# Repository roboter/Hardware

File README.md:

# HardwareModules
List of all my arduinos, ESPs, STM32s modules

## Directories

### [Arduino](/Arduino)
Various Arduino boards and development kits including Nano, Pro Mini, Leonardo, ATTINY85, and custom development boards.
<br/>

### [AVR](/AVR)
AVR microcontroller development boards and tools including Butterfly and STK500 programmer.
<br/>

### [CH582F](/CH582F)
CH582F microcontroller development resources.
<br/>

### [COMPONENTS](/COMPONENTS)
Hardware components including displays (SSD1306), sensors (WS2812, WS2812B, YF923), and linear sensors.
<br/>

### [Cypress](/Cypress)
Cypress microcontroller development boards including CY8CKIT-059.
<br/>

### [Displays](/Displays)
Display modules and libraries including:
* 1.7" SPI 128x160 OLED ST7735
* TM1637 Digital Tube LED Clock Display
* UTFT for Arduino Mega (PlatformIO)
* HD44780 LCD displays
* Nokia LCD5110 (PCD8544)
* SSD1306 OLED displays
* ST7789 TFT displays
* GM12864 GLCD modules
<br/>

### [EINK](/EINK)
E-ink display modules including Lilygo T5-4.7 inch displays.
<br/>

### [ESP](/ESP)
ESP32 and ESP8266 development boards including:
* Heltec WiFi Kit 8
* ESP32TTGO-OLED-18650
* TS V1.0 Esp32 1.44 TFT Display
* Wemos with Display
* ESP-01, ESP-03, ESP32-CAM
* T-Display-S3
* Various TTGO boards
<br/>

### [Geehy](/Geehy)
Geehy APM32 microcontroller development boards and SDKs.
<br/>

### [GigaDevice](/GigaDevice)
GigaDevice GD32 microcontroller boards including GD32VF103 (RISC-V) and GD32E232K.
<br/>

### [IC](/IC)
Integrated circuit datasheets and documentation.
<br/>

### [Modules](/Modules)
Various electronic modules including:
* Battery management modules
* CC1101 RF modules
* CP2102 USB-to-UART converters
* DS3231 RTC modules
* NRF24L01 wireless modules
* VS1053B MP3 player modules
* Motor drivers (A3967, l9110)
* Display modules (MAX7219, 8x8 RGB boards)
* And many more...
<br/>

### [NORDIC](/NORDIC)
Nordic Semiconductor development boards including nRF52810, nRF52833, and Embeetle boards.
<br/>

### [NXP](/NXP)
NXP microcontroller development boards including FRDM-K22F and FRDM-KL27Z.
<br/>

### [PROJECTS](/PROJECTS)
Complete hardware projects including LoRaWAN LR1262 designs with KiCad schematics and PCB files.
<br/>

### [Raspberry](/Raspberry)
Raspberry Pi RP2040-based boards including RP2040-Matrix and RP2040-Tiny.
<br/>

### [SHIELDS](/SHIELDS)
Arduino shields including:
* Multi Function Shield
* OPEN-SMART Rich Shield TWO
* VS153 MP3 Shield
* ZYA0031 IoT Training Kit
* Joystick shields
<br/>

### [STM32](/STM32)
STM32 microcontroller development boards including:
* BluePill, BlackPill
* NUCLEO series (F303K8, C031C6, L152RE, H563ZI)
* Discovery boards (F3DISCOVERY, F429-Discovery, F746G-Discovery)
* Mini development boards
* STM32F407VET6, STM32F103C8T6 variants
* WeAct Black Pill V3.0
* STLink programmer/debugger
<br/>

### [STM8](/STM8)
STM8 microcontroller development boards and documentation including STM8S103F3 development board.
<br/>

### [WCH](/WCH)
WCH microcontroller boards including CH32V003 series (RISC-V) development kits and examples.
<br/>

---

## Featured Boards

### Displays
* [1,7 SPI 128x160 OLED ST7735 <br/>
](/Displays/1,7_SPI_128x160_OLED_ST7735)

* <a href="/Displays/TM1637"> 4 Bits TM1637 Digital Tube LED Clock Display Module For Arduino Due UNO 2560 R3 <br/> </a>

* <a href="/Displays/UTFT"> UTFT for arduino mega (Paltformio) <br/>
</a>

### ESP
* <a href="ESP/HELTEC"> Heltec WiFi Kit 8 <br/> 
</a>
* <a href="ESP/ESP32TTGO-OLED-18650">ESP32TTGO-OLED-18650 <br/>
</a>

* <a href="ESP/TTGO">TS V1.0 Esp32 1.44 TFT Display MicroSD Card Slot Speakers WIFI Bluetooth Module <br/></a>

* <a href="ESP/Wemos-32-With-OLED">Wemos with Display<br/></a>

### STM32
* <a href="/STM32">STM32</a>

### STLink
* <a href="/STM32/STLink">STLink v2<br/></a>

### STM8 
* <a href="/STM8">STM8s103F3 Development board<br/>
 </a>

### Arduino
* <a href="/Arduino/Digistump-ATTINY85">Digistump ATTINY85<br/></a>

### GD32
* <a href="GigaDevice/GD32VF103">GD32VF103<br/></a>

### Cypress
* <a href="/Cypress/CY8CKIT-059">CY8CKIT-059<br/></a>

### Shields (arduino)
* <a href="SHIELDS/Multi_Function_Shield">Multi function Shield<br/></a>

### Battery Charger
* Battery charger modules can be found in [Modules/battery modules](/Modules/battery%20modules/)

### Modules
* <a href="/Modules/CP2102">CP2102 Micro USB to UART TTL Module 6Pin Serial Converter STC Replace FT232<br/></a>

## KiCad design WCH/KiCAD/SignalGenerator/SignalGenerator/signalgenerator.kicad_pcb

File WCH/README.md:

# WCH

This directory contains WCH (Nanjing Qinheng Microelectronics) microcontroller development boards and resources.

See [wiring.md](wiring.md) for general WCH (RISC-V) wiring and programming notes.

## Contents

### CH32V003-DEV-KIT
CH32V003 development kit based on RISC-V architecture. Contains:
<br/>
- Development board schematics
- Datasheets and reference manuals
- Example projects with SSD1306 OLED display
- I2C communication examples

### CH32V003EVT
CH32V003 evaluation board examples including:
- GPIO, UART, SPI, I2C examples
- Timer and PWM examples
- ADC and DMA examples
- Flash programming examples
- System configuration examples

### CH32V003J4M6
CH32V003J4M6 variant examples including:
- Blink examples
- Neopixel WS2812 examples
- KiCad project files
<br/>

### ch32v003f4p6-SignalGenerator
Complete signal generator project using CH32V003 and SI5351 clock generator chip. Includes:
- SI5351 driver implementation
- SSD1306 OLED display driver
- Documentation and schematics

### KiCAD
KiCad PCB design projects:
- CH32V003J4M6 development board
- Signal generator board design
- NE555 timer projects
- Gerber files for manufacturing

### Documentation
- CH32V003 datasheets and reference manuals
- WCH-Link programmer schematics
- Board pinout diagrams

All CH32V003 boards are based on RISC-V architecture, providing an open-source alternative to ARM Cortex-M0 microcontrollers.

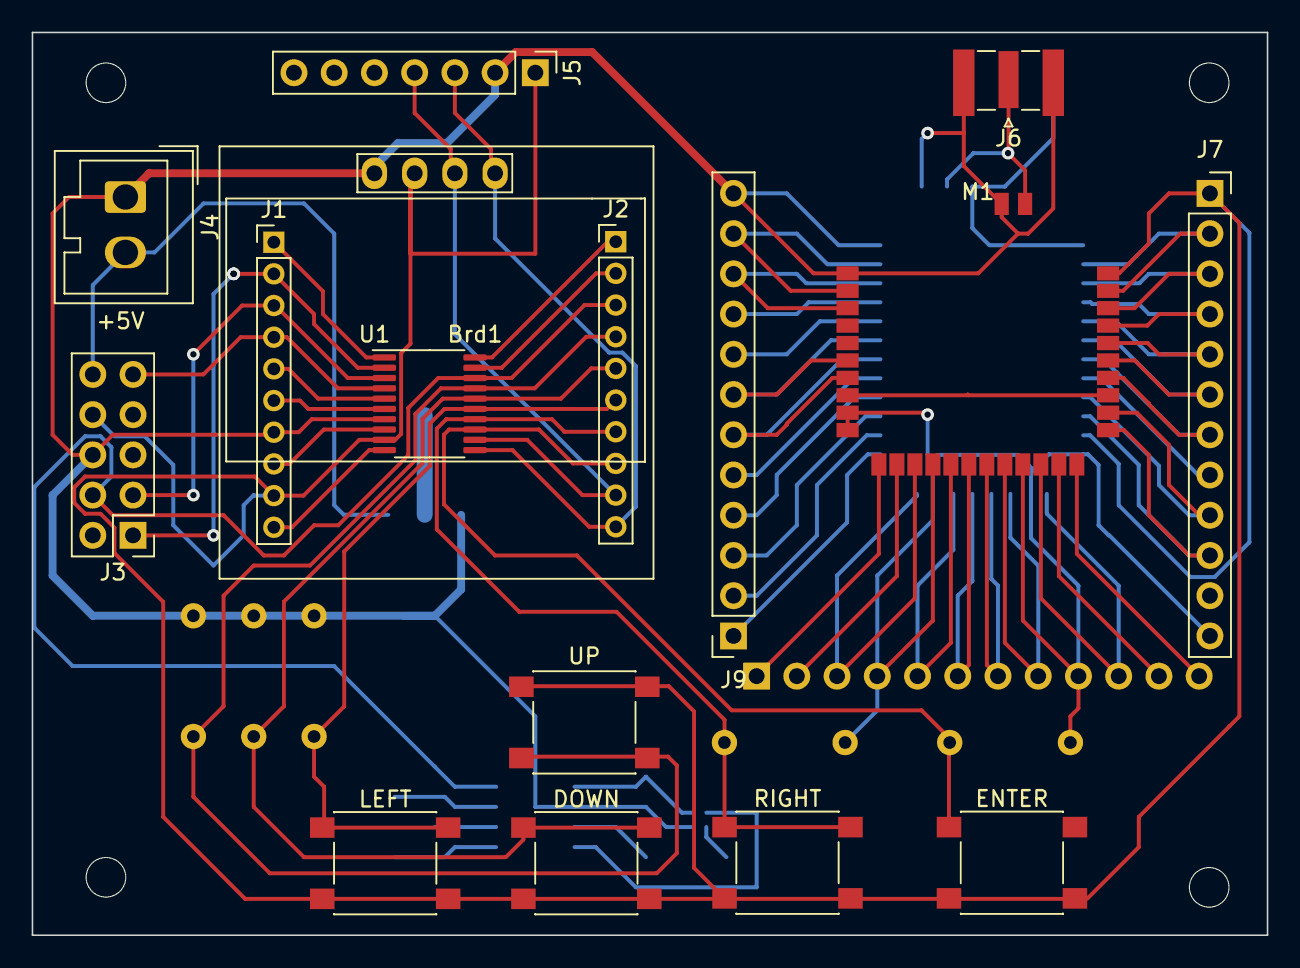
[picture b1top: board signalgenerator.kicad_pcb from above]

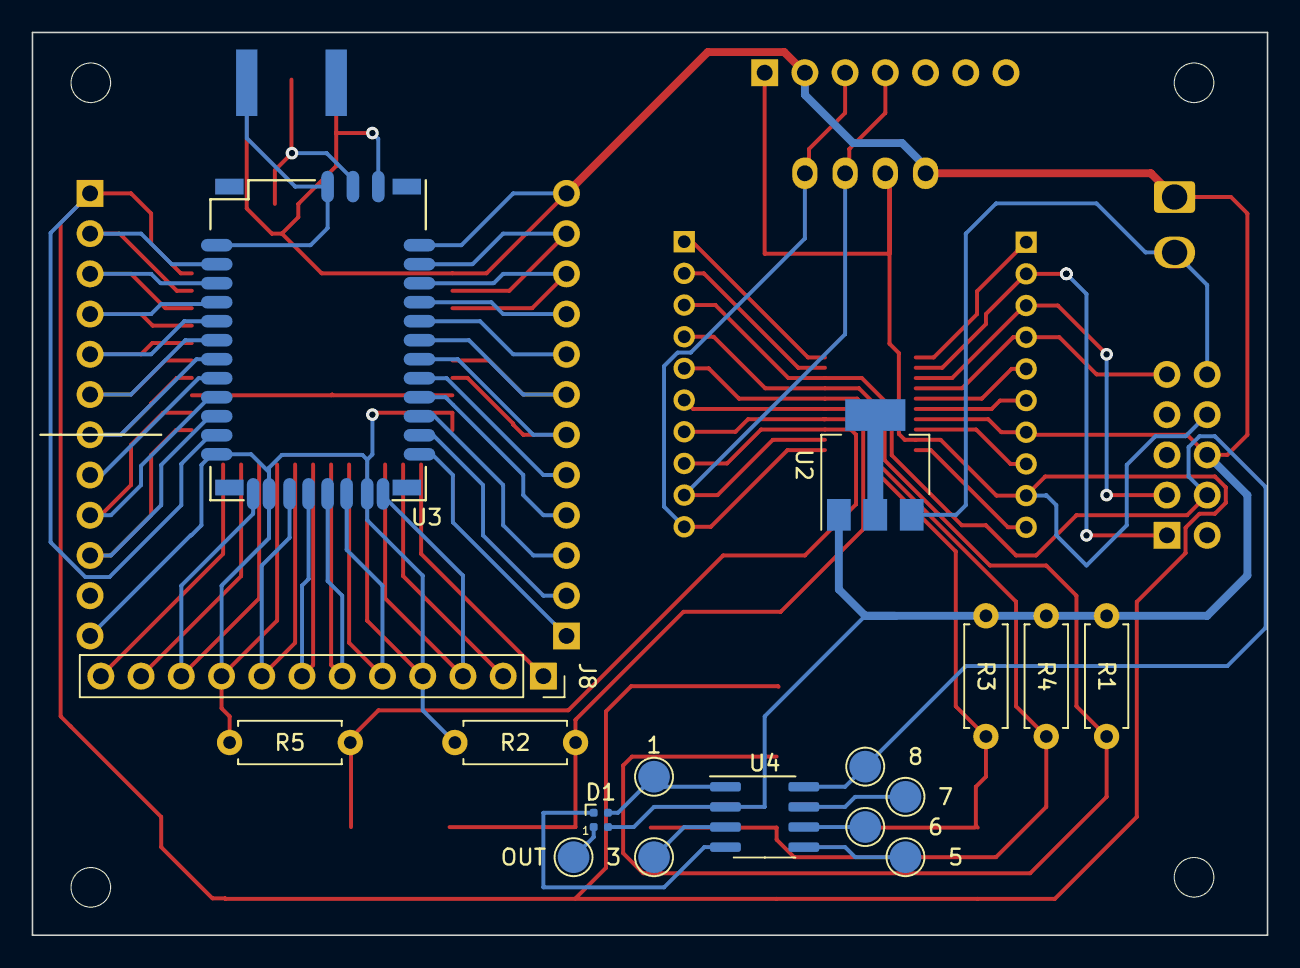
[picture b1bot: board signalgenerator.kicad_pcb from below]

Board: 2 copper layers, 78.0 x 57.0 mm, 33 parts (17 on the bottom side), 60 nets.

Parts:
1, 3, 5, 6, 7, 8: PC1; TestPoint_Pad_D2.0mm
Brd1: SSD1306; 128x64OLED
D1: SK6805; LED_SK6812_EC15_1.5x1.5mm
DOWN: RIGHT; SW_Push_1P1T_NO_6x6mm_H9.5mm
ENTER: ENTER; SW_Push_1P1T_NO_6x6mm_H9.5mm
J1, J2: Conn_01x10; PinHeader_1x10_P2.00mm_Vertical
J3: Conn_02x05_Odd_Even; PinHeader_2x05_P2.54mm_Vertical
J4: Conn_01x02; Wago_734-132_1x02_P3.50mm_Vertical
J5: Conn_01x07_Pin; PinHeader_1x07_P2.54mm_Vertical
J6: Conn_Coaxial; SMA_Samtec_SMA-J-P-X-ST-EM1_EdgeMount
J7, J8, J9: Conn_01x12; PinSocket_1x12_P2.54mm_Vertical
LEFT: LEFT; SW_Push_1P1T_NO_6x6mm_H9.5mm
M1: LR1262
OUT: PC1; TestPoint_Pad_D2.0mm
R1, R2, R3, R4, R5: 1K; R_Axial_DIN0207_L6.3mm_D2.5mm_P7.62mm_Horizontal
RIGHT: DOWN; SW_Push_1P1T_NO_6x6mm_H9.5mm
U1: CH32V003F4P6; TSSOP-20_4.4x6.5mm_P0.65mm
U2: AMS1117-3.3; SOT-223-3_TabPin2
U3: RN42N
U4: CH32V003J4M6; SOIC-8_3.9x4.9mm_P1.27mm
UP: UP; SW_Push_1P1T_NO_6x6mm_H9.5mm

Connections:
+3.3V: Brd1.2 (VCC), D1.4 (VDD), DOWN.2, ENTER.2, J1.9, J3.8, J5.1, J7.1, LEFT.2, M1.32 (3v3), RIGHT.2, U1.9 (VDD), U2.2 (VO), U3.11 (VDD), U4.4 (VDD), UP.2
+5V: J3.10, J4.2, U2.3 (VI)
/DOWN: J2.7, R2.1, RIGHT.1, U1.14 (PC4)
/ENTER: ENTER.1, J2.8, R5.1, U1.13 (PC3)
/LEFT: J2.6, LEFT.1, R3.1, U1.15 (PC5)
/RIGHT: DOWN.1, J2.5, R4.1, U1.16 (PC6)
/RST: J1.4, J3.9, U1.4 (PD7)
/RX: J1.2, J3.1, U1.2 (PD5)
/SCL: Brd1.3 (SCL), J2.9, J5.4, U1.12 (PC2)
/SDA: Brd1.4 (SDA), J2.10, J5.3, U1.11 (PC1)
/SWDIO: 8.1, J2.3, J3.4, U1.18 (PD1), U4.8 (PD1/PD4/PD5)
/TX: J1.3, J3.3, U1.3 (PD6)
/UP: J2.4, R1.1, U1.17 (PC7), UP.1
GND: Brd1.1 (GND), D1.2 (VSS), J1.7, J3.6, J4.1, J5.2, J6.2 (Ext), J7.12, J9.12, M1.1 (GND), M1.4 (GND), M1.5 (GND), M1.9 (GND), M1.10 (GND), M1.34 (GND), R1.2, R2.2, R3.2, R4.2, R5.2, U1.7 (VSS), U2.1 (GND), U3.1 (GND), U3.12 (GND), U3.25 (GND), U3.27 (GND), U3.28 (GND), U3.29 (GND), U4.2 (VSS)
J7_3: J7.10, M1.23 (UART-TX), U3.10 (PCM_OUT)
J7_4: J7.9, M1.24 (UART-RX), U3.9 (PCM_IN)
J7_5: J7.8, U3.8 (PCM_SYNC)
J7_6: J7.7, M1.26 (LPUART-RX), U3.7 (PCM_CLK)
J7_7: J7.6, M1.27 (PA8), U3.6 (SPI_CLK)
J7_8: J7.5, M1.28 (MOSI), U3.5 (RESET)
J7_9: J7.4, M1.29 (MISO), U3.4 (GPIO7)
J7_10: J7.3, M1.30 (SCK), U3.3 (GPIO6)
J7_11: J7.2, M1.31 (CS), U3.2 (SPI_MOSI)
J8_1: J8.1, M1.11 (PC13)
J8_2: J8.2, M1.12 (SWDIO)
J8_3: J8.3, M1.13 (I2C-SCL), U3.30 (AIO0)
J8_4: J8.4, M1.14 (I2C-SDA)
J8_5: J8.5, M1.15 (PA1), U3.31 (GPIO8)
J8_6: J8.6, M1.16 (PB3), U3.32 (GPIO9)
J8_7: J8.7, M1.17 (PB4), U3.33 (GPIO10)
J8_8: J8.8, M1.18 (SWCLK), U3.34 (GPIO11)
J8_9: J8.9, M1.19 (PA15)
J8_10: J8.10, M1.20 (PB5), U3.35 (AIO1)
J8_11: J8.11, M1.21 (PB8)
J8_12: J8.12, M1.22 (PA0)
J9_1: J9.1, U3.13 (UART_RX)
J9_2: J9.2, U3.14 (UART_TX)
J9_3: J9.3, U3.15 (UART_RTS)
J9_4: J9.4, U3.16 (UART_CTS)
J9_5: J9.5, M1.8 (PA10), M1.25 (LPUART-TX), U3.17 (USB_D+)
J9_6: J9.6, M1.7 (ADC), U3.18 (USB_D-)
J9_7: J9.7, M1.6 (VADDRF1V55), U3.19 (GPIO2)
J9_8: J9.8, U3.20 (GPIO3)
J9_9: J9.9, U3.21 (GPIO5)
J9_10: J9.10, M1.3 (NRST), U3.22 (GPIO4)
J9_11: J9.11, M1.2 (LR_BOOT), U3.23 (SPI_CSB)
unnamed: 1.1, D1.3 (DIN), U4.1 (PA1/PD6)
unnamed: D1.1 (DOUT), OUT.1
unnamed: J1.1, U1.1 (PD4)
unnamed: J1.5, U1.5 (PA1)
unnamed: J1.6, U1.6 (PA2)
unnamed: J1.8, U1.8 (PD0)
unnamed: J1.10, U1.10 (PC0)
unnamed: J2.1, U1.20 (PD3)
unnamed: J2.2, U1.19 (PD2)
unnamed: J6.1 (In), M1.33 (RF_ANT), U3.26 (RF_ANT)
unnamed: 3.1, U4.3 (PA2)
unnamed: 5.1, U4.5 (PC1)
unnamed: 6.1, U4.6 (PC2)
unnamed: 7.1, U4.7 (PC4)

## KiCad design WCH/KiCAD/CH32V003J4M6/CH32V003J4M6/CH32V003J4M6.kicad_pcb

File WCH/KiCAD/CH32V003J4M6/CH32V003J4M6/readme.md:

WCH: CH32V003J4M6
Flash: 16K
SRAM: 2K
Pin: 8 

https://github.com/cnlohr/ch32v003fun/blob/master/README.md

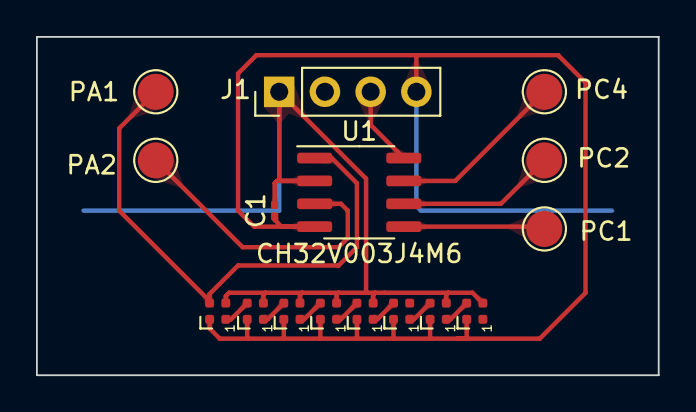
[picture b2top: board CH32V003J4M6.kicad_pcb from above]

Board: 2 copper layers, 34.5 x 18.8 mm, 17 parts (1 on the bottom side), 15 nets.

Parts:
BT1: Battery_Cell; BatteryHolder_Keystone_1058_1x2032
C1: 100nF; C_0201_0603Metric
D1, D2, D3, D4, D5, D6, D7, D8: SK6805; LED_SK6812_EC15_1.5x1.5mm
J1: Conn_01x04; PinHeader_1x04_P2.54mm_Vertical
TP1: PC1; TestPoint_Pad_D2.0mm
TP2: PC2; TestPoint_Pad_D2.0mm
TP3: PC4; TestPoint_Pad_D2.0mm
TP4: PA1; TestPoint_Pad_D2.0mm
TP5: PA2; TestPoint_Pad_D2.0mm
U1: CH32V003J4M6; SOIC-8_3.9x4.9mm_P1.27mm

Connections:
+3.3V: BT1.1 (+), C1.1, D1.4 (VDD), D2.4 (VDD), D3.4 (VDD), D4.4 (VDD), D5.4 (VDD), D6.4 (VDD), D7.4 (VDD), D8.4 (VDD), J1.4, U1.4 (VDD)
/SWIO: J1.3, U1.8 (PD1/PD4/PD5)
GND: BT1.2 (-), C1.2, D1.2 (VSS), D2.2 (VSS), D3.2 (VSS), D4.2 (VSS), D5.2 (VSS), D6.2 (VSS), D7.2 (VSS), D8.2 (VSS), J1.1, U1.2 (VSS)
unnamed: D1.3 (DIN), TP4.1, U1.1 (PA1/PD6)
unnamed: D1.1 (DOUT), D2.3 (DIN)
unnamed: D2.1 (DOUT), D3.3 (DIN)
unnamed: D3.1 (DOUT), D4.3 (DIN)
unnamed: D4.1 (DOUT), D5.3 (DIN)
unnamed: D5.1 (DOUT), D6.3 (DIN)
unnamed: D6.1 (DOUT), D7.3 (DIN)
unnamed: D7.1 (DOUT), D8.3 (DIN)
unnamed: TP5.1, U1.3 (PA2)
unnamed: TP1.1, U1.5 (PC1)
unnamed: TP2.1, U1.6 (PC2)
unnamed: TP3.1, U1.7 (PC4)

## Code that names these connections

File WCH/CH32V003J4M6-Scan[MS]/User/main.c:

/********************************** (C) COPYRIGHT *******************************
 * File Name          : main.c
 * Author             : WCH
 * Version            : V1.0.0
 * Date               : 2023/12/25
 * Description        : Main program body.
 *********************************************************************************
 * Copyright (c) 2021 Nanjing Qinheng Microelectronics Co., Ltd.
 * Attention: This software (modified or not) and binary are used for 
 * microcontroller manufactured by Nanjing Qinheng Microelectronics.
 *******************************************************************************/

/*
 *@Note
 *Multiprocessor communication mode routine:
 *Master:USART1_Tx(PD5)\USART1_Rx(PD6).
 *This routine demonstrates that USART1 receives the data sent by CH341 and inverts
 *it and sends it (baud rate 115200).
 *
 *Hardware connection:PD5 -- Rx
 *                    PD6 -- Tx
 *
 *
 *Info : WCH-LinkE  mode:RV version 2.15
 */

#include "debug.h"
#include <ch32v00x_i2c.h>
#include <ch32v00x_gpio.h>
#include <ch32v00x_rcc.h>
#include <stdio.h>

/* Global define */
#define LED_PIN GPIO_Pin_1
#define LED_PORT GPIOC

#define BUTTONPORT GPIOC
#define UP      GPIO_Pin_7
#define RIGHT GPIO_Pin_6
#define LEFT    GPIO_Pin_5
#define DOWN    GPIO_Pin_4
#define ENTER GPIO_Pin_3

#define TIMEOUT 100  // Define a timeout value
/*********************************************************************
 * @fn      GPIO_Toggle_INIT
 *
 * @brief   Initializes GPIOA.0
 *
 * @return  none
 */
void GPIO_Buttons_INIT(void) {
    GPIO_InitTypeDef GPIO_InitStructure = { 0 };

    // Enable the clock for the GPIO port
    RCC_APB2PeriphClockCmd(RCC_APB2Periph_GPIOC, ENABLE);

    // Configure the pins as input floating
    GPIO_InitStructure.GPIO_Pin = ENTER | UP | DOWN | RIGHT | LEFT;
    GPIO_InitStructure.GPIO_Mode = GPIO_Mode_IN_FLOATING;
    GPIO_Init(BUTTONPORT, &GPIO_InitStructure);
}

/*********************************************************************
 * @fn      IIC_Init
 *
 * @brief   Initializes the IIC peripheral.
 *
 * @return  none
 */
void IIC_Init() {
    GPIO_InitTypeDef GPIO_InitStructure = { 0 };
    I2C_InitTypeDef I2C_InitTSturcture = { 0 };

    RCC_APB2PeriphClockCmd( RCC_APB2Periph_GPIOC | RCC_APB2Periph_AFIO, ENABLE);
    RCC_APB1PeriphClockCmd( RCC_APB1Periph_I2C1, ENABLE);

    GPIO_InitStructure.GPIO_Pin = GPIO_Pin_2; // PC2 - SCL
    GPIO_InitStructure.GPIO_Mode = GPIO_Mode_AF_OD;
    GPIO_InitStructure.GPIO_Speed = GPIO_Speed_50MHz;
    GPIO_Init( GPIOC, &GPIO_InitStructure);

    GPIO_InitStructure.GPIO_Pin = GPIO_Pin_1; // PC1 - SDA
    GPIO_InitStructure.GPIO_Mode = GPIO_Mode_AF_OD; // Alternative function + Open Drain
    GPIO_InitStructure.GPIO_Speed = GPIO_Speed_50MHz;
    GPIO_Init( GPIOC, &GPIO_InitStructure);

    I2C_InitTSturcture.I2C_ClockSpeed = 400000;
    I2C_InitTSturcture.I2C_Mode = I2C_Mode_I2C;
    I2C_InitTSturcture.I2C_DutyCycle = I2C_DutyCycle_16_9;
//    I2C_InitTSturcture.I2C_OwnAddress1 = 0x00;//address;
    I2C_InitTSturcture.I2C_Ack = I2C_Ack_Enable;
    I2C_InitTSturcture.I2C_AcknowledgedAddress = I2C_AcknowledgedAddress_7bit;
    I2C_Init( I2C1, &I2C_InitTSturcture);

    I2C_Cmd( I2C1, ENABLE);

    I2C_AcknowledgeConfig( I2C1, ENABLE);
}

void I2C_SendByte(uint8_t address, uint8_t data) {
    while(I2C_GetFlagStatus(I2C1, I2C_FLAG_BUSY) != RESET);

    I2C_GenerateSTART(I2C1, ENABLE);

    while(!I2C_CheckEvent(I2C1, I2C_EVENT_MASTER_MODE_SELECT));

    I2C_Send7bitAddress(I2C1, address << 1, I2C_Direction_Transmitter);

    while(!I2C_CheckEvent(I2C1, I2C_EVENT_MASTER_TRANSMITTER_MODE_SELECTED));

    while(I2C_GetFlagStatus(I2C1, I2C_FLAG_TXE) == RESET);

    I2C_SendData(I2C1, data);

    while(!I2C_CheckEvent(I2C1, I2C_EVENT_MASTER_BYTE_TRANSMITTED));

    I2C_GenerateSTOP(I2C1, ENABLE);
}

void I2C_Scan() {
    printf("Scanning I2C bus...\r\n");
    for (uint16_t address = 0; address < 128; address++) {
        // Wait until the I2C bus is ready
        while(I2C_GetFlagStatus(I2C1, I2C_FLAG_BUSY) != RESET);

        // Generate start condition
        I2C_GenerateSTART(I2C1, ENABLE);

        // Wait for the start condition to be generated
        while(!I2C_CheckEvent(I2C1, I2C_EVENT_MASTER_MODE_SELECT));

        // Send the address with the write bit
        I2C_Send7bitAddress(I2C1, address << 1, I2C_Direction_Transmitter);
        // Wait for the address to be acknowledged with a timeout
        uint32_t timeout_counter = 0;
        while (!I2C_CheckEvent(I2C1, I2C_EVENT_MASTER_TRANSMITTER_MODE_SELECTED)) {
            if (timeout_counter++ > TIMEOUT) {
                //            printf("Timeout at address 0x%02X\n", address);
                break;
            }
        }

        // If the address was acknowledged, print it
        if (timeout_counter <= TIMEOUT) {
            printf("0x%02X ", address  /*<< 1*/);
        } else {
            printf(". ");
        }

        // Generate stop condition
        I2C_GenerateSTOP(I2C1, ENABLE);
    }
    printf("\r\n");
}

int main(void) {
    // Initialize system and GPIO
    SystemInit();
    Delay_Init();
    USART_Printf_Init(115200);
    GPIO_Buttons_INIT();
    // Setup internal peripherals

    IIC_Init();
    //I2C_init_Display();
    int previous = 0;

    while (1)
    {
        // Toggle PC1
        // Read the button values
        int up = GPIO_ReadInputDataBit(BUTTONPORT, UP);
        int right = GPIO_ReadInputDataBit(BUTTONPORT, RIGHT);
        int left = GPIO_ReadInputDataBit(BUTTONPORT, LEFT);
        int down = GPIO_ReadInputDataBit(BUTTONPORT, DOWN);
        int enter = GPIO_ReadInputDataBit(BUTTONPORT, ENTER);

        // Check which button is pressed
        if (up && previous != UP) {

            printf("UP\n");
            printf("SystemClk:%d\r\n",SystemCoreClock);
            previous = UP;
        } else if (right && previous != RIGHT) {

            printf("RIGHT\n");
            previous = RIGHT;
        } else if (left && previous != LEFT) {

            printf("LEFT\n");
            previous = LEFT;
        } else if (down && previous != DOWN) {

            printf("DOWN\n");
            previous = DOWN;
        } else if (enter && previous != ENTER) {

            printf("ENTER button pressed\n");
            previous = ENTER;
            I2C_Scan();
        }

    }
}

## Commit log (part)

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2023-04-05 Initial
2023-04-05 init
2023-04-06 SSD1306
2023-04-06 another display project
2023-04-07 ssd1306 works
2023-04-10 nucleo F303
2023-04-15 FRDM-KL27Z
2023-04-16 nordic + soldering kot
2023-04-16 Nordic examples
2023-04-28 NORDIC EXAMPLE
2023-05-03 bluetooth led
2023-05-03 little formatting
2023-05-05 GD32E232K-start
2023-05-09 Gd32
2023-05-18 ESP/arduino/gigadevice
2023-05-21 VS1053 MP3 Shield
2023-05-22 no spaces
2023-06-11 YF923-1515LED
2023-06-11 Format
2023-06-11 cleanup
2023-06-11 embeetle project
2023-06-11 embeetle UTFT library
2023-06-23 F32F103
2023-06-23 nucleo
2023-06-25 bluepill
2023-06-28 bluepill codes
2023-07-02 geehy
2023-07-02 Board
2023-07-02 geehy datasheet
2023-07-02 readme
2023-07-02 move readme
2023-07-02 fix geehy readme
2023-07-02 test HTML readme
2023-07-02 revert
2023-07-02 nokia display arduino
2023-07-03 NOKIA DISPLAY
2023-07-07 mapple-mini-blink
2023-07-07 Tim3 blink
2023-07-08 F429
2023-07-08 bluepill/blackpill
2023-07-09 printf OpenOCD mac
2023-07-09 semihosting
2023-07-22 discovery
2023-07-30 removing debug
2023-07-30 ignore debug
2023-07-30 remove debug
2023-07-31 SWO, USB working
2023-07-31 toggle via USB Com port
2023-08-01 test eeprom
2023-08-04 UMFT200Xd
2023-08-04 usb drivers and utilites
2023-08-25 modules
2023-08-25 F746
2023-08-25 F746 BSP
2023-09-08 Rich shield
2023-10-07 smartSield
2023-10-08 CP2040 matrix
2023-10-12 ds18b20
2023-10-15 embeetle projects
2023-10-24 more projects
2023-10-24 Blink + printf
2023-11-12 USBTransfer
2023-11-12 embeetle discovery-429i
2023-11-13 dir rename
2023-11-14 more info
2023-11-15 C031C6+ssd1306
2023-11-16 libraries rename
2023-11-18 user manual
2023-11-25 lvgl embeetle
2023-11-25 no need for template
2023-12-03 WCH + ssd1306
2023-12-13 LVGL FOR 429
2023-12-13 LV Demo
2023-12-15 LVGL source
2023-12-20 fix nokia display arduino sketch
2023-12-20 deleting debug
2023-12-24 SignalGenerator
2023-12-24 rename
2023-12-24 BUTTONS
2023-12-24 singal generator
2023-12-25 CH32V003J4M6
2023-12-26 F303-PWM
2023-12-26 Neopixel
2023-12-26 neopizel
2024-01-03 vscode ignore
2024-01-03 nove bluepill
2024-01-31 wch pcb
2024-01-31 neopixel-round
2024-03-02 projects
2024-03-23 lvport
2024-04-06 128x64
2024-04-06 beetle logo
2024-05-09 menu
2024-08-08 win668
2024-08-20 I2C scanner
2024-08-30 PCF8574
2024-09-12 OLED_draw_bmp_by_size
    Added a method to draw a bitmap from one coordinate with the size instead of a secondary coordinate to end.
2024-10-12 rp2040-matrix
2024-10-12 moved
2024-10-16 152RE
2024-10-16 Si5351
2024-10-20 nucleo 303
2024-10-21 rp2040Tiny
2024-10-21 ESP image
2024-10-21 DEVKIT
2024-10-21 003 examples
2024-10-21 WCH ChipId
2024-10-23 DHTLin zip
2024-11-18 WCH Blink
2024-11-18 sysinit
2024-11-19 WCH ch32v003j4m6
2024-11-23 Adding library to project
2024-11-23 library update
2024-12-01 lolin
2024-12-29 WCH SignalGenerator
2024-12-29 raname
2024-12-29 debug file
2025-01-05 lilin c3 mini pro
2025-01-05 signal generator
2025-01-20 ESPs
2025-01-25 pro mini
2025-01-25 cnc shield
2025-01-27 LitteFS
2025-02-10 arduino modules
2025-03-15 arduinoisp
2025-03-18 pricture from SD card
2025-03-18 fromsdcard
2025-03-24 more STM projects
2025-03-25 testarduinp
2025-03-26 rearrange
2025-03-27 stm8
2025-03-27 template
2025-03-30 No debug functionality
2025-03-30 LEDCMSIS
2025-03-30 Working SPL platformio example
2025-03-30 Blink works
2025-03-31 BlackPill
2025-03-31 something is working
2025-03-31 upgrade
2025-03-31 another hal blink
2025-03-31 move hal blink
2025-03-31 blink
2025-03-31 Display kinda works
2025-04-01 remove sdk
2025-04-01 display
2025-04-07 freertos-blink
2025-04-07 woking VCP example
2025-04-08 mini SPI flash
2025-04-20 GEEHY SEGGER Project
2025-04-21 F303
2025-05-01 wireless charger
2025-05-03 NRF24L01
2025-05-22 F407VET6 black pill
2025-05-27 f407+cc1101
2025-06-01 cc1101
2025-06-01 eval demo
2025-06-01 move to platformio
2025-06-04 DSOLSWVILA CC1101
2025-06-07 working CC1101
2025-06-07 CC1101 Recive worcs
2025-06-11 buttefly
2025-06-13 battery modules
2025-06-13 st7735
2025-06-13 filename is too long
2025-06-14 smart display NRF24
2025-06-15 display faster speed
2025-06-15 nRF24 working (another library)
2025-06-15 F407_NRF24
2025-06-15 receiving joystick command
2025-06-16 WORKING Library example
2025-06-16 WORKING LIBRARY EXAMPLE TX
2025-06-16 WORKING RX
2025-06-16 WORKING TX
2025-06-16 WTF WORKS
2025-06-16 TANK 1 byte transfer
2025-06-16 TANK 1 byte works
2025-06-16 CRC works
2025-06-22 butterfly rev07
2025-06-22 more modules
2025-07-03 smart
2025-07-05 stm32 tank
2025-07-05 restore
2025-07-05 stm32F10rC8T6
2025-07-06 adafruit library
2025-07-07 use another library with SPI interface
2025-08-16 STM32H750
2025-08-16 gitignore
2025-08-17 KEIL Came working projects
2025-08-17 CUBEIDE WORKING PROJECTS
2025-08-17 OV2640 not working
2025-08-17 FIXING WITH CURSOR
2025-08-17 FIXING AFTER CURSOR
2025-09-02 gitignore for obj files
2025-09-03 Removing custom i2c library
2025-09-12 si5351 found with i2c scanner
2025-09-30 STM43H750
2025-10-02 New sigal generator board
2025-10-29 book
2025-11-19 signal generator UI
2025-12-06 images fix
2026-01-02 readmes generated
2026-01-02 more readmes
2026-01-05 vscode project for discovery3
2026-01-05 readmes
2026-01-13 F303 + MSP430
2026-01-16 Blink example with unofficial driverLib
2026-01-21 ti example
2026-03-23 fix readme
2026-03-23 ignore debug folder
2026-04-24 H563ZI
2026-05-05 TI ACTBP
2026-05-05 docs
